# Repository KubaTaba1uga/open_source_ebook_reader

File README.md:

# open_source_ebook_reader
Open source ebook reader device.

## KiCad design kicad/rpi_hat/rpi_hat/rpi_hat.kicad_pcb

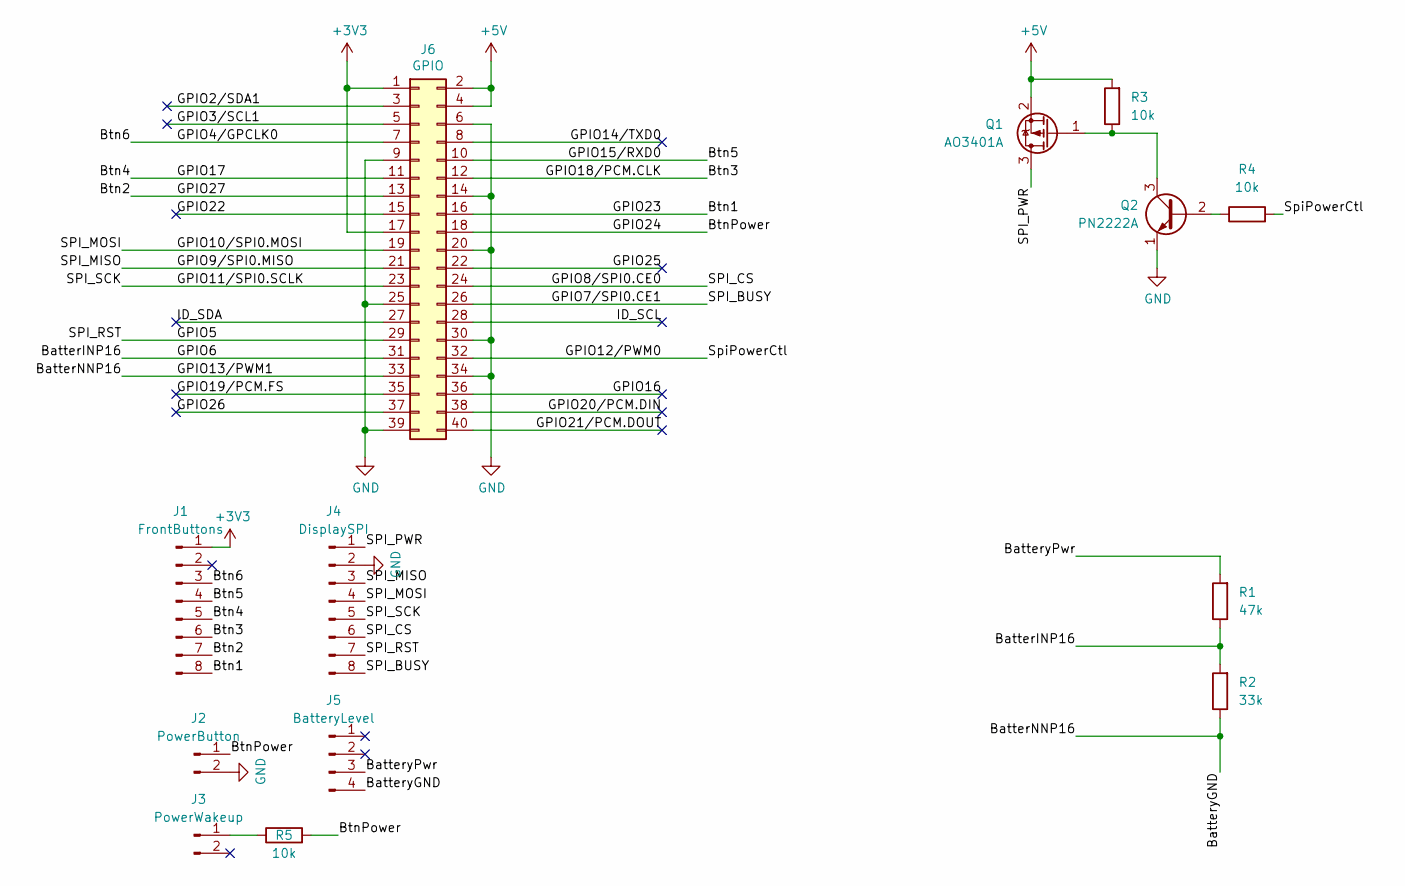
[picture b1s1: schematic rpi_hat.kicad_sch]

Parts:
J1: FrontButtons; JST_XH_S8B-XH-A_1x08_P2.50mm_Horizontal
J2: PowerButton; JST_XH_S2B-XH-A_1x02_P2.50mm_Horizontal
J3: PowerWakeup; JST_XH_S2B-XH-A_1x02_P2.50mm_Horizontal
J4: DisplaySPI; JST_PH_S8B-PH-K_1x08_P2.00mm_Horizontal
J5: BatteryLevel; JST_XH_S4B-XH-A_1x04_P2.50mm_Horizontal
J6: GPIO; PinSocket_2x20_P2.54mm_Vertical
Q1: AO3401A; SOT-23
Q2: PN2222A; TO-92_Inline
R1: 47k; R_Axial_DIN0207_L6.3mm_D2.5mm_P10.16mm_Horizontal
R2: 33k; R_Axial_DIN0207_L6.3mm_D2.5mm_P10.16mm_Horizontal
R3, R4, R5: 10k; R_Axial_DIN0207_L6.3mm_D2.5mm_P10.16mm_Horizontal

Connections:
+3V3: J1.1, J6.1, J6.17
+5V: J6.2, J6.4, Q1.2 (S), R3.2
/BatterINP16: J6.31, R1.1, R2.2
/BatterNNP16: J5.4, J6.33, R2.1
/BatteryPwr: J5.3, R1.2
/Btn1: J1.8, J6.16
/Btn2: J1.7, J6.13
/Btn3: J1.6, J6.12
/Btn4: J1.5, J6.11
/Btn5: J1.4, J6.10
/Btn6: J1.3, J6.7
/BtnPower: J2.1, J6.18, R5.2
/GPIO2/SDA1: J6.3
/GPIO3/SCL1: J6.5
/GPIO5: J4.7, J6.29
/GPIO7/SPI0.CE1: J4.8, J6.26
/GPIO8/SPI0.CE0: J4.6, J6.24
/GPIO9/SPI0.MISO: J4.3, J6.21
/GPIO10/SPI0.MOSI: J4.4, J6.19
/GPIO11/SPI0.SCLK: J4.5, J6.23
/GPIO12/PWM0: J6.32, R4.2
/GPIO14/TXD0: J6.8
/GPIO16: J6.36
/GPIO19/PCM.FS: J6.35
/GPIO20/PCM.DIN: J6.38
/GPIO21/PCM.DOUT: J6.40
/GPIO22: J6.15
/GPIO25: J6.22
/GPIO26: J6.37
/ID_SCL: J6.28
/ID_SDA: J6.27
/SPI_PWR: J4.1, Q1.3 (D)
GND: J2.2, J4.2, J6.6, J6.9, J6.14, J6.20, J6.25, J6.30, J6.34, J6.39, Q2.1 (E)
unnamed: J3.1 (Pin_1_1), R5.1
unnamed: Q1.1 (G), Q2.3 (C), R3.1
unnamed: Q2.2 (B), R4.1

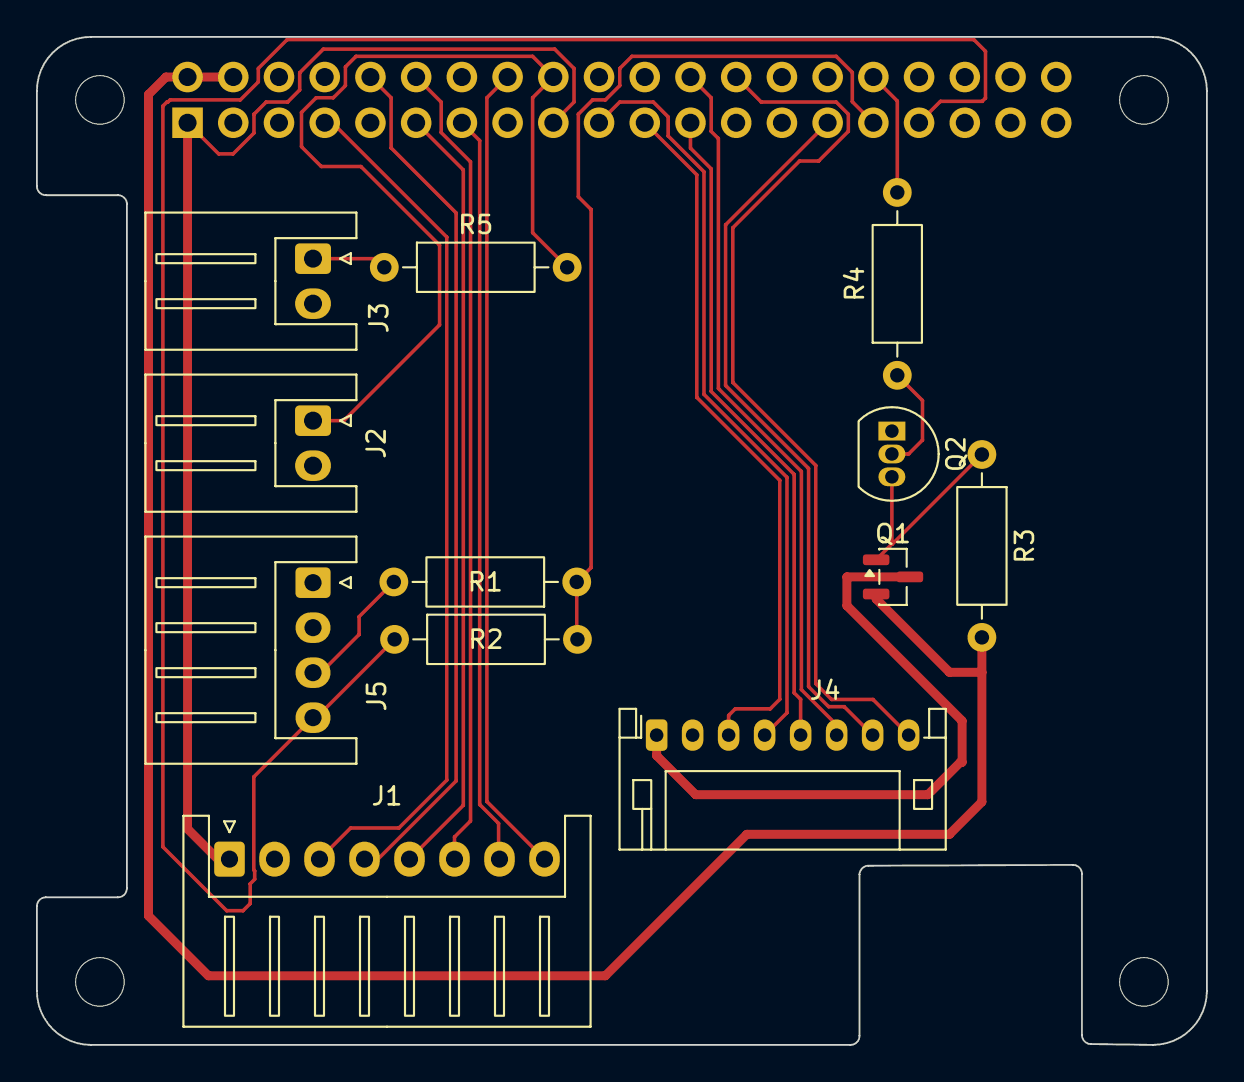
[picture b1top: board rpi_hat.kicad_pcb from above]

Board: 2 copper layers, 65.0 x 56.0 mm, 17 parts (1 on the bottom side), 24 nets.

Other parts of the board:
MH1, MH2, MH3, MH4: MountingHole_2.7mm_M2.5

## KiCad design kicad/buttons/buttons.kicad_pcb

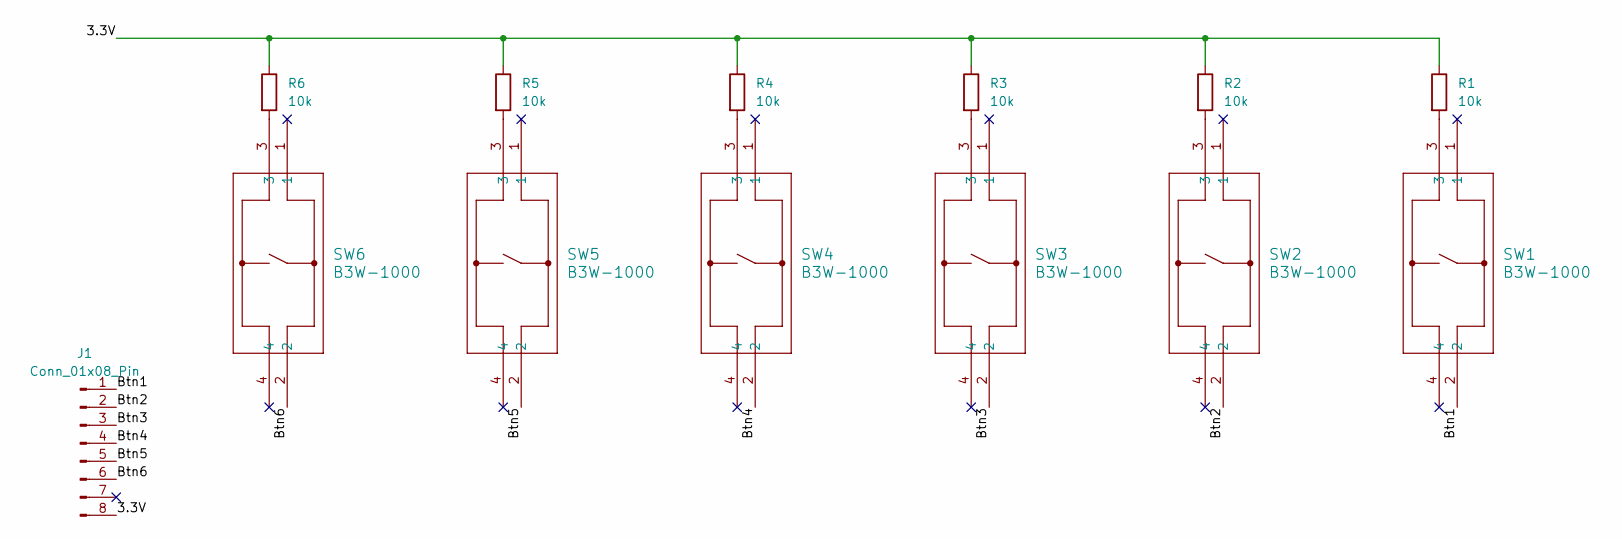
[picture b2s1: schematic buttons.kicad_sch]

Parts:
J1: Conn_01x08_Pin; JST_XH_S8B-XH-A_1x08_P2.50mm_Horizontal
R1, R2, R3, R4, R5, R6: 10k; R_Axial_DIN0207_L6.3mm_D2.5mm_P10.16mm_Horizontal
SW1, SW2, SW3, SW4, SW5, SW6: B3W-1000; SW_B3W-1000_OMR

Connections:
/3.3V: J1.8, R1.1, R2.1, R3.1, R4.1, R5.1, R6.1
/Btn1: J1.1, SW1.2
/Btn2: J1.2, SW2.2
/Btn3: J1.3, SW3.2
/Btn4: J1.4, SW4.2
/Btn5: J1.5, SW5.2
/Btn6: J1.6, SW6.2
unnamed: R1.2, SW1.3
unnamed: R2.2, SW2.3
unnamed: R3.2, SW3.3
unnamed: R4.2, SW4.3
unnamed: R5.2, SW5.3
unnamed: R6.2, SW6.3

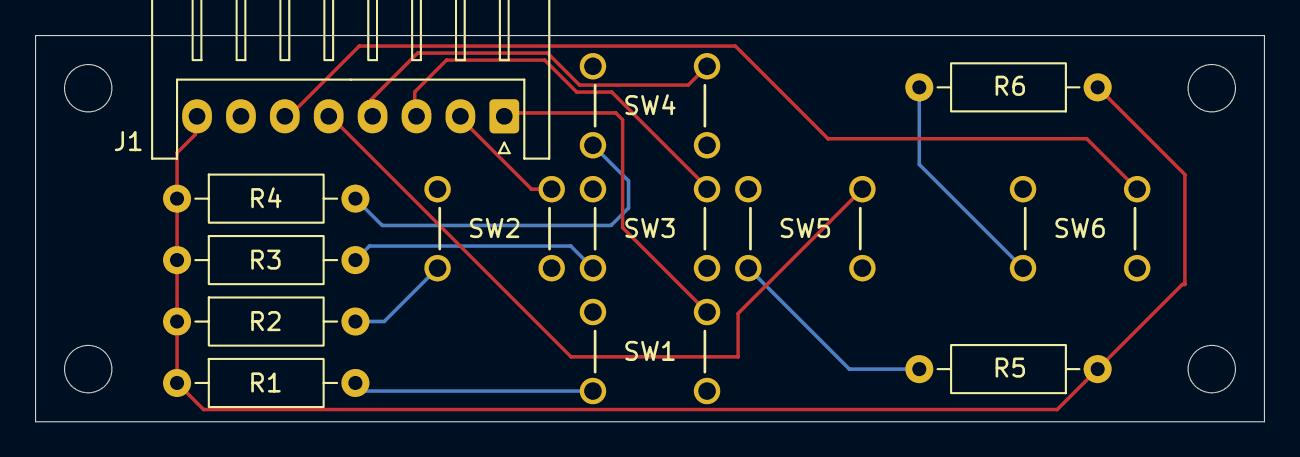
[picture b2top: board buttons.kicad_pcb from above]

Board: 2 copper layers, 70.0 x 22.0 mm, 17 parts (0 on the bottom side), 13 nets.

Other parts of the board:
MH2, MH2#2, MH2#3, MH2#4: MountingHole_2.7mm_M2.5

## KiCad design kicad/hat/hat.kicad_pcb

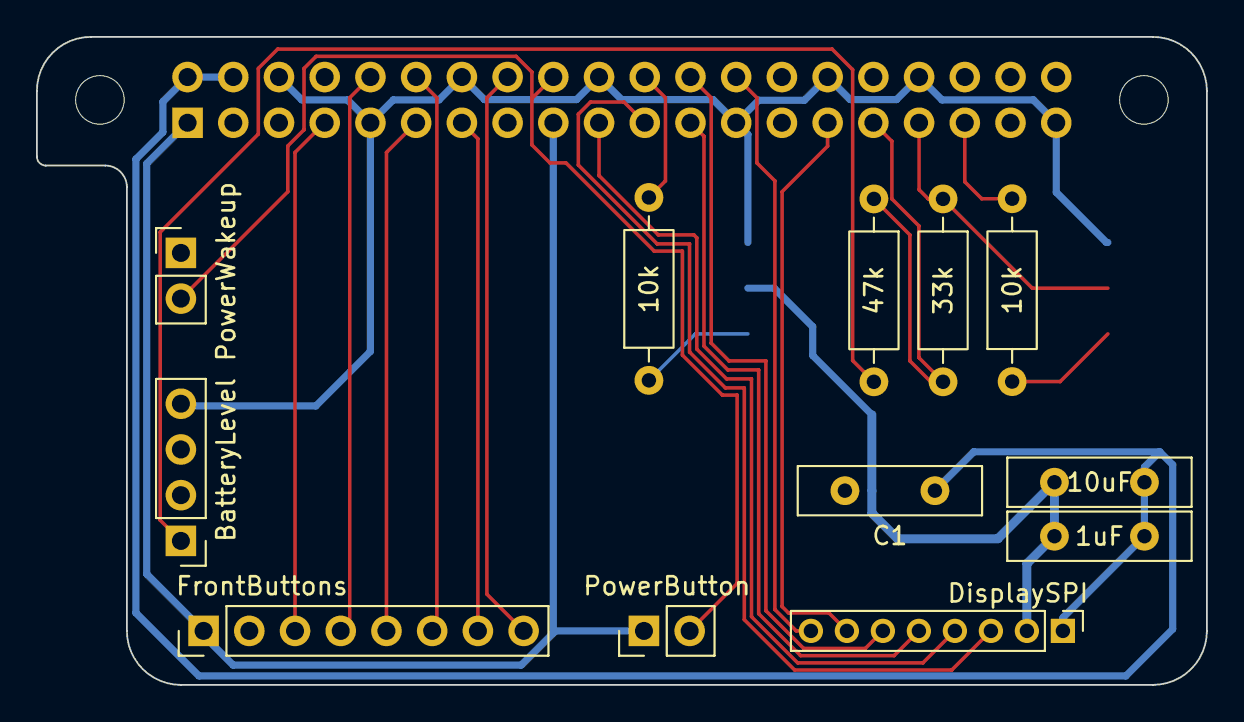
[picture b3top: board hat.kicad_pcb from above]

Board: 2 copper layers, 65.0 x 36.0 mm, 15 parts (1 on the bottom side), 19 nets.

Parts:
C1: 100nF; C_Disc_D10.0mm_W2.5mm_P5.00mm
C2: 1uF; C_Disc_D10.0mm_W2.5mm_P5.00mm
C3: 10uF; C_Disc_D10.0mm_W2.5mm_P5.00mm
J1: GPIO; PinSocket_2x20_P2.54mm_Vertical
J2: FrontButtons; PinHeader_1x08_P2.54mm_Vertical
J3: DisplaySPI; PinHeader_1x08_P2.00mm_Vertical
J4: BatteryLevel; PinHeader_1x04_P2.54mm_Vertical
J5: PowerButton; PinHeader_1x02_P2.54mm_Vertical
J6: PowerWakeup; PinHeader_1x02_P2.54mm_Vertical
MH1, MH2: MountingHole_2.7mm_M2.5
R1, R4: 10k; R_Axial_DIN0207_L6.3mm_D2.5mm_P10.16mm_Horizontal
R2: 47k; R_Axial_DIN0207_L6.3mm_D2.5mm_P10.16mm_Horizontal
R3: 33k; R_Axial_DIN0207_L6.3mm_D2.5mm_P10.16mm_Horizontal

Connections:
+3V3: J1.1, J1.17, J2.1, J5.1
+5V: C1.1, C2.1, C3.1, J1.2, J1.4, J3.1
/BatterINP16: J1.31, R2.1, R3.2
/BatteryPwr: J4.1, R2.2
/Btn1: J1.16, J2.8
/Btn2: J1.13, J2.7
/Btn3: J1.12, J2.6
/Btn4: J1.11, J2.5
/Btn5: J1.10, J2.4
/Btn6: J1.7, J2.3
/BtnPower: J1.18, J5.2, J6.2 (Pin_2_2)
/GPIO5: J1.29, J3.7
/GPIO7/SPI0.CE1: J1.26, J3.8
/GPIO8/SPI0.CE0: J1.24, J3.6
/GPIO9/SPI0.MISO: J1.21, J3.3
/GPIO10/SPI0.MOSI: J1.19, J3.4
/GPIO11/SPI0.SCLK: J1.23, J3.5
/SPI_GND: C1.2, C2.2, C3.2, J3.2
GND: J1.6, J1.9, J1.14, J1.20, J1.25, J1.30, J1.33, J1.34, J1.39, J4.4, R3.1

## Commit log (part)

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2026-05-16 init repo
2026-05-16 Init repo (#2)
    * init repo
    * WIP
2026-05-16 add stm32mp135d odyssey board
2026-05-16 Add support for stm32mp135d odyssey (#3)
2026-05-16 improve docs
2026-05-16 add app with deps
2026-05-16 install libgpiod 1.6.5
2026-05-16 add gdb support
2026-05-16 add gdb and openocd support to odyssey board
2026-05-16 add cross compile script for ebook reader
2026-05-18 bannerize src code
2026-05-18 fix typo
2026-05-18 cleanup
2026-05-18 cleanup c.d
2026-05-18 Add ebook reader app (#4)
    * improve docs
    * add ebook reader app
    * install libgpiod 1.6.5
    * add gdb support
    * add gdb and openocd support to odyssey board
    * add cross compile script for ebook reader
2026-05-28 start hat in kicad
2026-05-28 addd pcb layer to hat
2026-05-28 addd display on off switch to hat
2026-05-28 add footprints to hat
2026-05-30 start buttons board
2026-05-30 finish buttons board
2026-05-30 improve buttons board
2026-06-03 add adc1 channel 2
2026-06-05 add ADC for battery measurement
2026-06-05 connect adc to battery
2026-06-05 fix hat bugs
